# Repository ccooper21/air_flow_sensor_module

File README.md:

# Trion Air Flow Sensor Module

This is a replica of the optional air flow sensor module for use with the high voltage DC power supply in Trion HE Plus 1400 and HE Plus 2000 electronic air cleaners circa 2005.  Later revisions of the power supply have this module integrated into the main PCB.

## Background and Motivation

My home, built in 2005, has two Carrier HVAC systems, one for each floor.  Each system includes a Carrier branded electronic air cleaner unit that I determined was originally manufactured by Trion.  Each unit utilizes a power supply that converts the AC voltage from the wall (i.e. 110VAC) to a high DC voltage (i.e. 10,000VDC or more).  As designed, the high voltage part of a unit is only intended to operate when the HVAC system's blower fan is on and moving air through the system.  My guess is that this is necessary to avoid the build-up of ozone.  Irrespective, a switching mechanism is expected to be utilized to only energize the high voltage part of the air cleaner at appropriate times.  In my units, this was achieved by the installation of an air flow sensor module in each unit when it was initially installed.  Unfortunately, both modules failed within about two years of installation.  In both cases, the failure mode was that the thermistor disc, which senses air flow, literally fell off of its leads, presumably due to thermal stress.

*This photo shows the main PCB of the high voltage DC power supply.  The pigtail is for the high voltage output.  I blew the soldered in fuse, so I replaced it with a fuse holder and a removable fuse.  The 2x3 pin connector for the air flow sensor module is visible in the bottom right corner.*

*This photo shows the front of the original air flow sensor PCB minus the failed thermistor.  I let the magic smoke out of the LM358 IC during one of my experiments, so I replaced it with a socket and a new IC.  The pads for the thermistor can be seen on the left side in the middle.*

*This photo shows the back of the original air flow sensor PCB.*

On several occasions, without success, I have tried to find suitable replacement thermistors, and performed various experiments with the broken modules in support of this effort.  Probably due to my limited soldering experience, I managed to lift some of the pads off of their PCBs in the process.  With the expectation that I will eventually get the air cleaners functioning again, I used this as an opportunity to learn the process of PCB design and manufacturing using a simple circuit that I already understood.

## Replacing the Failed Thermistors

When I realized that my air cleaners were no longer working as expected, I investigated and found both failed thermistor discs in the power supply tray of their respective units.  The thermistors are quite small and the their leads originally covered most of each disc's faces.  Hence, unfortunately, there are no markings to provide a hint as to the manufacturer or specifications.

*This photo shows the failed thermistor discs and their relative size.*

Here is what I know about the thermistors:

* The [Trion product manual](https://www.trioniaq.com/getfile2.aspx?fileid=9024) states:

> The AFS utilizes a thermistor, which when electrically powered heats up to approximately 130&#8457;. The AFS stabilizes at this temperature and while the HVAC system blower is in operation, air flows through the ductwork, creating a vacuum effect that pulls cooler air over the hot surface of the thermistor. This air movement cools down the thermistor which allows the AFS to register that the HVAC system blower is moving air and the Electronic Air Cleaner must be powered to provide air cleaning.

* I measured the diameter of the discs as ~4.3mm/170mils.  I measured the thickness of one disc as ~1.3mm/50mils and of the other disc as ~2.0mm/80mils.  The discrepancy in thickness is due to residual solder from the original lead on one disc face.

* The mechanism by which the air flow sensor module's switching functionality works is by the use of an LM358 op-amp that compares the voltage from a voltage divider leg, including the thermistor, against the voltage from a reference voltage divider leg.  Based on the actual resistances of the voltage divider components, switching will occur when the thermistor's resistance is between around 180&#8486; and 210&#8486;.  When the thermistor's resistance rises above this range (i.e. there is no air flow) the output circuit closes causing the air cleaner's high voltage part to deenergize.  Inversely, when the thermistor's resistance drops below this range (i.e. the HVAC system's blower is on), the output circuit opens causing the air cleaner's high voltage part to energize.

* The voltage divider leg containing the thermistor has a voltage drop of about 18VDC.  The thermistor is in series with a 68&#8486; resistor.

Given the above, I expect that a suitable replacement thermistor will have these characteristics:

* Be a PTC thermistor
* Have a maximum operating voltage of more than 18V
* Have a resistance less than 180&#8486; at 25&#8451;, which is often documented on thermistor data sheets
* Have a resistance less than 180&#8486; at the thermistor's nominal temperature with air flow
* Have a resistance greater than 180&#8486; at ~55&#8451; in still air
* Be self heating, and reach a temperature of ~55&#8451; when driven with a ~70mA current (i.e. 18V / (68&#8486; + 180&#8486;))
* If non-linear, have a switching temperature less than 55&#8451;

The challenge in finding a thermistor meeting this criteria is that many thermistors do not have the relevant attributes documented, especially non-linear ones.  Even if they are documented, they are not necessarily parameterized for search on the large electronic distributors' websites.  Further, most non-linear thermistors have a much higher switching temperature than what is required for this application.

## KiCad

### Third-Party Footprints

[Bourns 3362P potentiometer](https://github.com/mcous/kicad-lib/blob/master/footprints/bourns.pretty/BOURNS-3362P_pot.kicad_mod)

* Thanks to Mike Cousins for posting this footprint on GitHub!  I have modified the footprint to make its line widths consistent with the line widths of the other footprints that I'm using.

## References

[Trion HE Plus 1400 and HE Plus 2000 Data Sheet](https://www.trioniaq.com/getfile2.aspx?fileid=8983)

[Trion HE Plus 1400 and HE Plus 2000 Product Manual](https://www.trioniaq.com/getfile2.aspx?fileid=9024)

Replacement [Trion 248090-001 Air Flow Sensor Module](http://www.trionparts.com/248090-001-air-flow-sensor-board.html) **(No Longer Available)**

* The module shown here appears to be an earlier revision than the ones that I have based on its date code.  Its traces are shaped a little different and it uses a different optoisolator or similar.  The thermistor is visible.

Replacement [Trion 348818-001 Power Supply](http://www.trionparts.com/348818-001-power-pack-circuit-board.html) **(with integrated air flow sensor)**

* The components shown in the bottom right corner of the PCB implement the air flow sensor module.  These are the same components and design as the earlier off-board air flow sensor module, except that the optoisolator has been replaced with a transistor and ceramic capacitor.   The thermistor is visible along the bottom side on the right.

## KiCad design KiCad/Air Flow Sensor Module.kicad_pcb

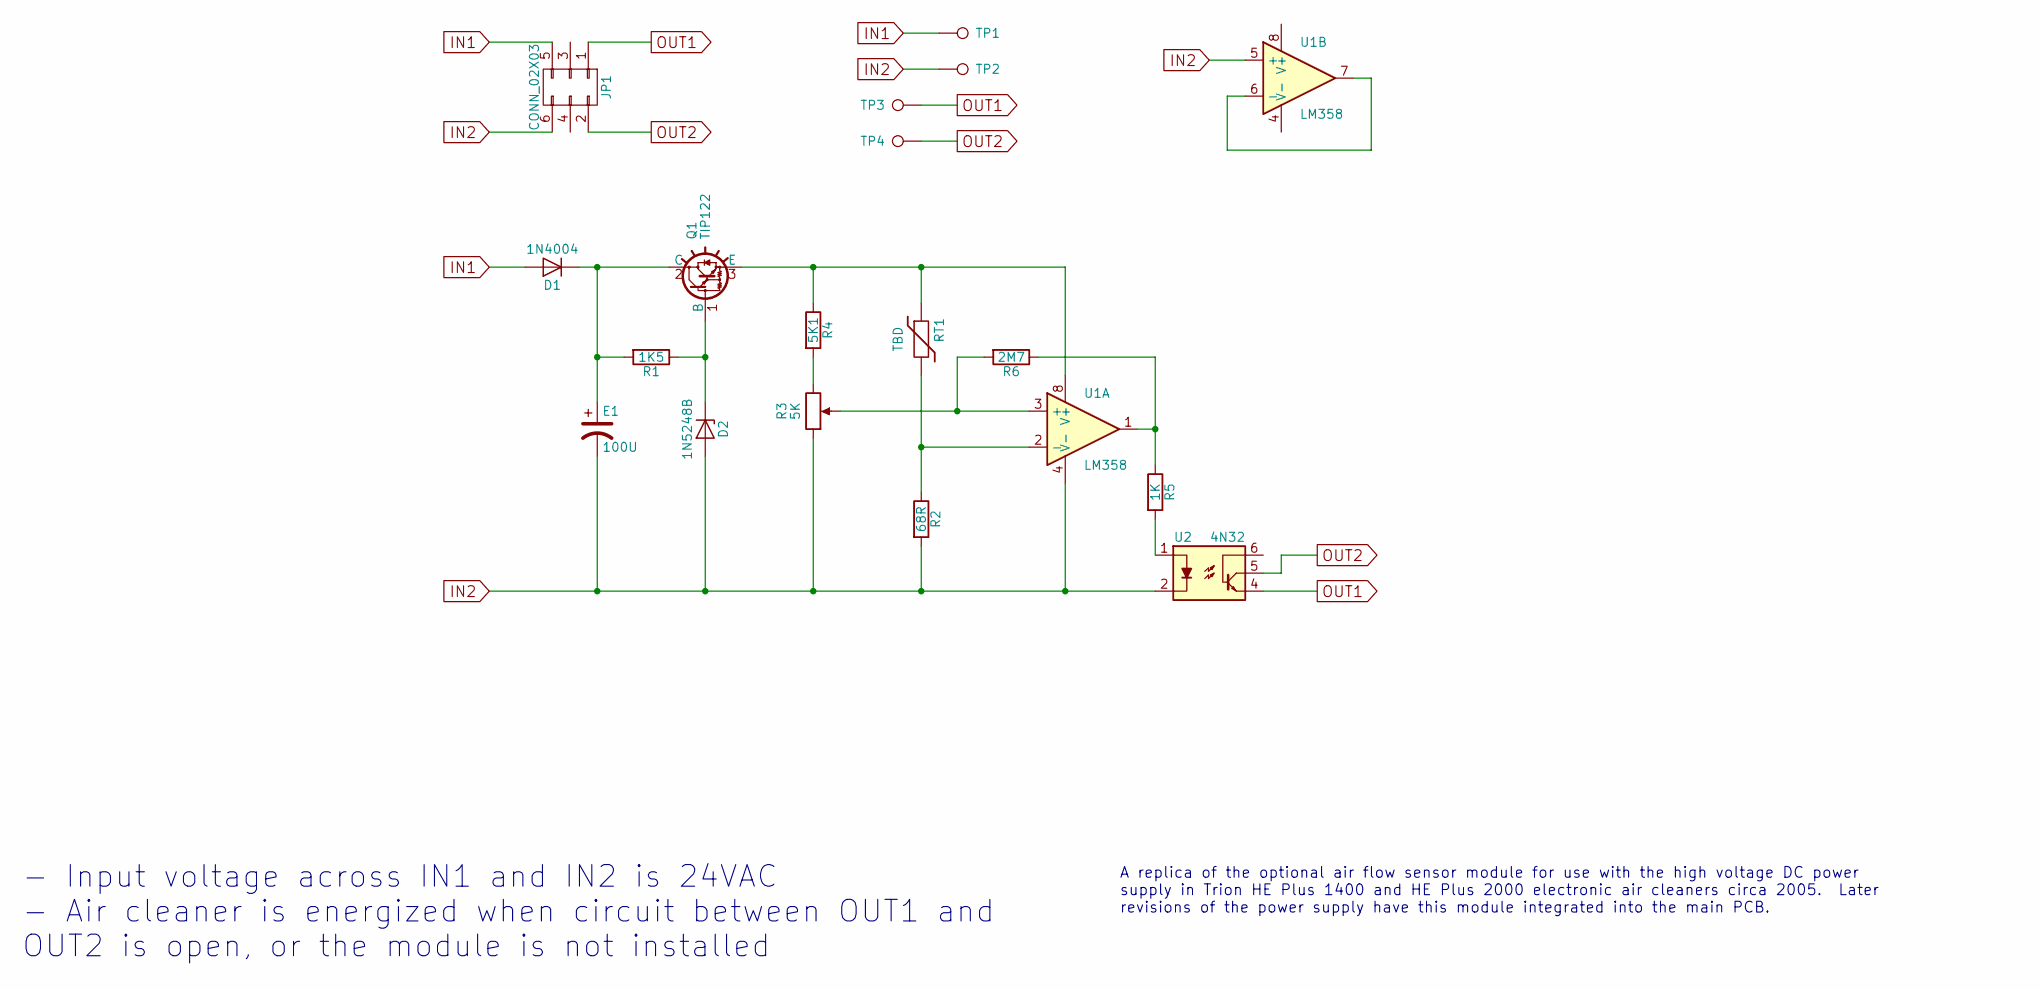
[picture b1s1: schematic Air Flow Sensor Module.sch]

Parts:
D1: 1N4004; D_DO-41_SOD81_P10.16mm_Horizontal
D2: 1N5248B; D_DO-35_SOD27_P10.16mm_Horizontal
E1: 100U; CP_Radial_D8.0mm_P3.50mm
JP1: CONN_02X03; Pin_Header_Angled_2x03_Pitch2.54mm
Q1: TIP122; TO-220
R1: 1K5; R_Axial_DIN0207_L6.3mm_D2.5mm_P10.16mm_Horizontal
R2: 68R; R_Axial_DIN0414_L11.9mm_D4.5mm_P20.32mm_Horizontal
R3: 5K; BOURNS-3362P_pot
R4: 5K1; R_Axial_DIN0207_L6.3mm_D2.5mm_P10.16mm_Horizontal
R5: 1K; R_Axial_DIN0207_L6.3mm_D2.5mm_P10.16mm_Horizontal
R6: 2M7; R_Axial_DIN0207_L6.3mm_D2.5mm_P10.16mm_Horizontal
RT1: TBD; R_Box_L8.4mm_W2.5mm_P5.08mm
TP1, TP2, TP3, TP4: TEST_1P; SolderWirePad_single_1mmDrill
U1: LM358; DIP-8_W7.62mm_Socket
U2: 4N32; DIP-6_W7.62mm_Socket

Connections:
IN1: D1.2 (A), JP1.5, TP1.1
IN2: D2.2 (A), E1.2, JP1.6, R2.2, R3.1, TP2.1, U1.4 (V-), U1.5 (+), U2.2
unnamed: D1.1 (K), E1.1, Q1.2 (C), R1.2
unnamed: D2.1 (K), Q1.1 (B), R1.1
unnamed: Q1.3 (E), R4.1, RT1.1, U1.8 (V+)
unnamed: R2.1, RT1.2, U1.2 (-)
unnamed: R3.2, R6.2, U1.3 (+)
unnamed: R3.3, R4.2
unnamed: R5.1, R6.1, U1.1
unnamed: R5.2, U2.1
unnamed: U1.6 (-), U1.7
OUT1: JP1.1, TP3.1, U2.4
OUT2: JP1.2, TP4.1, U2.5

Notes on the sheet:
- Input voltage across IN1 and IN2 is 24VAC - Air cleaner is energized when circuit between OUT1 and OUT2 is open, or the module is not installed
A replica of the optional air flow sensor module for use with the high voltage DC power supply in Trion HE Plus 1400 and HE Plus 2000 electronic air cleaners circa 2005. Later revisions of the power supply have this module integrated into the main PCB.

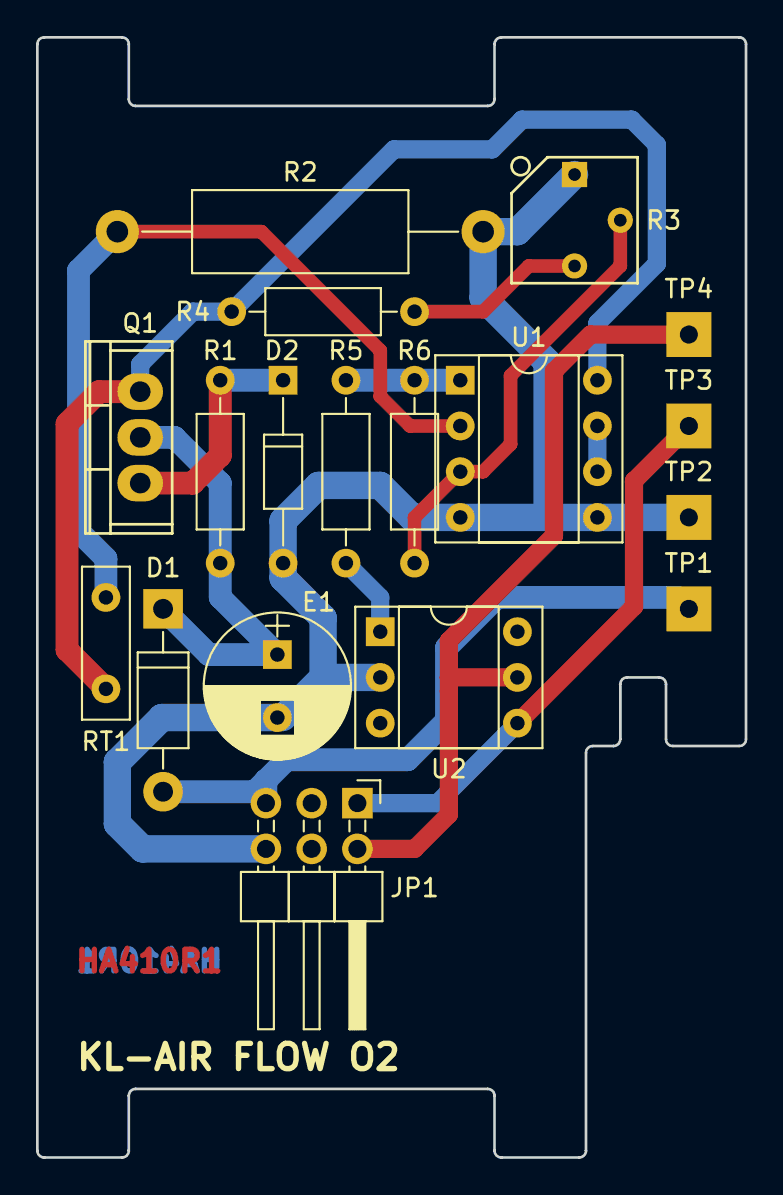
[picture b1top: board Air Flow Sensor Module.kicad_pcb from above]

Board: 2 copper layers, 39.4 x 62.2 mm, 18 parts (0 on the bottom side), 13 nets.

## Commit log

2017-03-14 Corrected and adjusted component reference positions on front silkscreen
2017-03-28 Restructured images referenced by primary "README.md" file
2017-03-28 Moved directory containing Gerber files to project root
2017-03-28 Renamed directory containing KiCad files
2017-03-28 Adjusted traces beneath components U1 and U2 to more closely match original
2017-03-28 Replaced component R2 footprint to allow for resistor size of proper wattage
